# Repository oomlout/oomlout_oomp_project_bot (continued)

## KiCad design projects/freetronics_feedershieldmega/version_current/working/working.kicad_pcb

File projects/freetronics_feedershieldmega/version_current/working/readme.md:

# OOMP Project  
## FeederShieldMega  by freetronics  
  
oomp key: oomp_projects_flat_freetronics_feedershieldmega  
(snippet of original readme)  
  
Feeder Shield Mega  
==================  
Copyright 2018-2020 Freetronics Pty Ltd  www.freetronics.com    
  
Pick and place feeder controller for DIY feeders. Compatible with the  
0816 feeders designed by MGRL:  
  
  https://docs.mgrl.de/maschine:pickandplace:feeder:0816feeder  
  
These feeders are commonly used with DIY pick and place machines  
running OpenPNP:  
  
  http://openpnp.org  
  
Run the MGRL feeder control firmware.  
  
Adds an I2C display that can be used for reporting events and part  
counts.  
  
Uses 10-way IDC cables to connect batches of 4 feeders. Mates to the  
MGRL0816 Feeder Link board, which bridges across the 4-pin connections  
on 4 feeders mounted side by side.  
  
Features:  
  
 * 24 feeder outputs  
 * PWM output and feedback input  
 * GND and 5V supply to feeders  
 * Software controlled feeder power  
 * 128x32 OLED  
  
You can view more online at:  
  
  http://www.freetronics.com.au/fsm  

INSTALLATION  
------------  
The design is saved as an EAGLE project. EAGLE PCB design software is  
available from www.cadsoftusa.com free for non-commercial use. To use  
this project download it and place the directory containing these files  
into the "eagle" directory on your computer. Then open EAGLE and  
navigate to the project.  

DISTRIBUTION  
------------  
The specific terms of distribution of this project are governed by the  
license referenced below.  

LICENSE  
-------  
Licensed under the TAPR Open Hardware License (www.tapr.org/OHL).  
The "license" folder within this repository also contains a copy of  
this license i  
  full source readme at [readme_src.md](readme_src.md)  
  
source repo at: [https://github.com/freetronics/FeederShieldMega](https://github.com/freetronics/FeederShieldMega)  
## Board  

## Schematic  

[schematic pdf](working_schematic.pdf)  
## Images

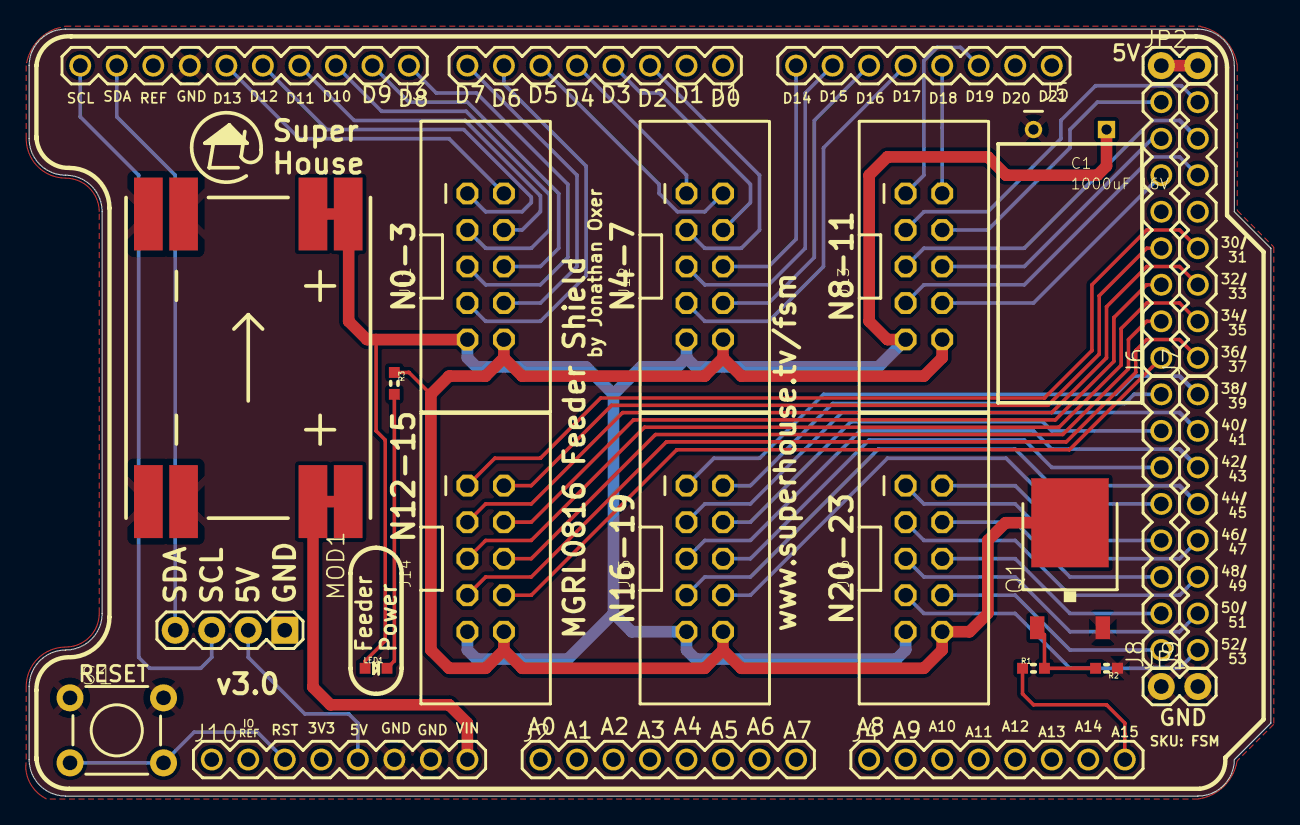
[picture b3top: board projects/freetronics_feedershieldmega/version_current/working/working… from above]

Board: 2 copper layers, 86.4 x 53.3 mm, 27 parts (0 on the bottom side), 60 nets.

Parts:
C1: 1000uF 16V; CPOL-RADIAL-5.08-10X18-FLAT
J1, J5: Digital_0_7; 1X08-P-BELOW
J2, J4: Analog; 1X08-P-BELOW
J3: Digital_8_13; 1X10-P-BELOW
J6: Digital_22_36; 1X08-P-BELOW
J7: Digital_23_37; 1X08-P-BELOW
J8: Digital_38_52; 1X08-P-BELOW
J9: Digital_39_53; 1X08-P-BELOW
J10: Power; 1X08-P-BELOW
J11, J12, J13, J14, J15, J16: M02X5-SHROUDED; 2X05-2.54-SHROUDED
JP1, JP2: 1X02-P-BELOW
LED1: GREEN; LED-0603
MOD1: OLED-I2C128X32-0.91-HEADER; OLED-128X32-0.91-HEADER
MOD2: DC5V3A-SMT
Q1: NTD5867NLT4G; DPACK
R1: 1K; R0603
R2: 10K; R0603
R3: 470R; R0603
S1: TACTILE-PTH-6MM

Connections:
5V: J10.5, MOD1.VCC
5V_2: JP2.1, JP2.2
A15: J4.8, R1.1
D2: J1.3, J12.3
D3: J1.4, J12.4
D4: J1.5, J12.1
D5: J1.6, J12.2
D6: J1.7, J11.7
D7: J1.8, J11.8
D8: J3.1, J11.5
D9: J3.2, J11.6
D10: J3.3, J11.3
D11_MOSI: J3.4, J11.4
D12_MISO: J3.5, J11.1
D13_SCK: J3.6, J11.2
D14: J5.8, J12.6
D15: J5.7, J12.5
D16: J5.6, J12.8
D17: J5.5, J12.7
D18: J5.4, J13.2
D19: J5.3, J13.1
D22: J6.8, J13.4
D23: J7.8, J13.3
D24: J6.7, J13.6
D25: J7.7, J13.5
D26: J6.6, J13.8
D27: J7.6, J13.7
D30: J6.4, J14.2
D31: J7.4, J14.1
D32: J6.3, J14.4
D33: J7.3, J14.3
D34: J6.2, J14.6
D35: J7.2, J14.5
D36: J6.1, J14.8
D37: J7.1, J14.7
D38: J8.8, J15.2
D39: J9.8, J15.1
D40: J8.7, J15.4
D41: J9.7, J15.3
D42: J8.6, J15.6
D43: J9.6, J15.5
D44: J8.5, J15.8
D45: J9.5, J15.7
D46: J8.4, J16.2
D47: J9.4, J16.1
D48: J8.3, J16.4
D49: J9.3, J16.3
D50_MISO: J8.2, J16.6
D51_MOSI: J9.2, J16.5
D52_SCK: J8.1, J16.8
D53: J9.1, J16.7
F_5V: C1.1, J11.9, J12.9, J13.9, J14.9, J15.9, J16.9, LED1.A, MOD2.3A, MOD2.3B
F_GND: J11.10, J12.10, J13.10, J14.10, J15.10, J16.10, Q1.2, R3.1
GND: C1.2, J3.7, J10.6, J10.7, JP1.1, JP1.2, MOD1.GND, MOD2.1A, MOD2.1B, MOD2.4A, MOD2.4B, Q1.3, R2.1, S1.1, S1.2
unnamed: Q1.1, R1.2, R2.2
unnamed: LED1.C, R3.2
RESET: J10.3, S1.3, S1.4
SCL: J3.10, MOD1.SCL
SDA: J3.9, MOD1.SDA
VIN: J10.8, MOD2.2A, MOD2.2B

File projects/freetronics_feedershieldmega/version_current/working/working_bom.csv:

"Id";"Designator";"Footprint";"Quantity";"Designation";"Supplier and ref";
1;"JP2,JP1";"1X02-P-BELOW";2;"";;;
2;"J12,J13,J11,J14,J15,J16";"2X05-2.54-SHROUDED";6;"M02X5-SHROUDED";;;
3;"J9";"1X08-P-BELOW";1;"Digital_39_53";;;
4;"J10";"1X08-P-BELOW";1;"Power";;;
5;"R3";"R0603";1;"470R";;;
6;"R2";"R0603";1;"10K";;;
7;"J3";"1X10-P-BELOW";1;"Digital_8_13";;;
8;"C1";"CPOL-RADIAL-5.08-10X18-FLAT";1;"1000uF 16V";;;
9;"J2,J4";"1X08-P-BELOW";2;"Analog";;;
10;"LED1";"LED-0603";1;"GREEN";;;
11;"R1";"R0603";1;"1K";;;
12;"J5,J1";"1X08-P-BELOW";2;"Digital_0_7";;;
13;"MOD2";"DC5V3A-SMT";1;"DC5V3A-SMT";;;
14;"J7";"1X08-P-BELOW";1;"Digital_23_37";;;
15;"J8";"1X08-P-BELOW";1;"Digital_38_52";;;
16;"J6";"1X08-P-BELOW";1;"Digital_22_36";;;
17;"Q1";"DPACK";1;"NTD5867NLT4G";;;
18;"MOD1";"OLED-128X32-0.91-HEADER";1;"OLED-I2C128X32-0.91-HEADER";;;
19;"S1";"TACTILE-PTH-6MM";1;"";;;

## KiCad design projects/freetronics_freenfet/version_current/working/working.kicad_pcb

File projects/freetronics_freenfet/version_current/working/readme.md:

# FREENFET by freetronics  
This is a harvested standardized copy of a project from github.  
The original project can be found at:  
https://github.com/freetronics/FREENFET  
Please consult that link for additional, details, files, and license information.  
Note: It was auto harvested and if the original repo had more than one board file or anything out of the ordinary the files here are likely not representative.

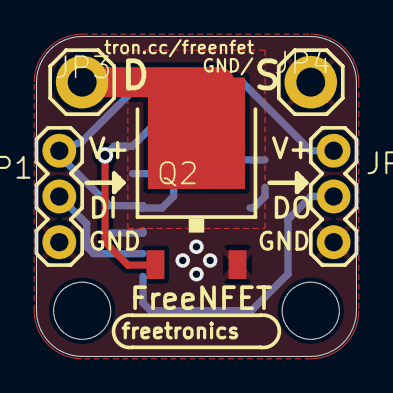
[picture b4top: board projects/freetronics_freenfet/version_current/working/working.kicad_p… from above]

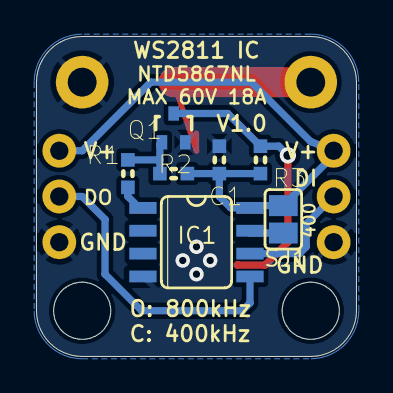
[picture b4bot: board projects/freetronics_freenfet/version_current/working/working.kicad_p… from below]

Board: 2 copper layers, 17.8 x 17.8 mm, 14 parts (7 on the bottom side), 9 nets.

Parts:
@HOLE0, @HOLE1: (no value)
C1: 1uF 0603; 0603
IC1: WS2811-SOP8; SO08-SKINNYPADS
JP1: IN; 1X03
JP2: OUT; 1X03
JP3: DRAIN; 1X01LARGE
JP4: SOURCE; 1X01LARGE
Q1: RJU003N03; SOT32-3
Q2: NTD5867NLT4G; DPACK
R1: 1K; 0603
R2, R3: 10K; 0603
SJ1: LOW-SPEED; SJ

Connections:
D: JP3.1, Q2.2
DIN: IC1.6, JP1.2
DOUT: IC1.5, JP2.2
GND: C1.2, IC1.4, JP1.3, JP2.3, JP4.1, Q1.2, Q2.3
unnamed: IC1.7, SJ1.1
unnamed: Q1.1, R1.1, R2.1
unnamed: Q1.3, Q2.1, R3.1
OUT1: IC1.1, R1.2
VCC: C1.1, IC1.8, JP1.1, JP2.1, R2.2, R3.2, SJ1.2

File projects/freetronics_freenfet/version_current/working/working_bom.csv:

"Id";"Designator";"Footprint";"Quantity";"Designation";"Supplier and ref";
1;"JP1";"1X03";1;"IN";;;
2;"JP4";"1X01LARGE";1;"SOURCE";;;
3;"JP2";"1X03";1;"OUT";;;
4;"JP3";"1X01LARGE";1;"DRAIN";;;
5;"Q2";"DPACK";1;"NTD5867NLT4G";;;
6;"@HOLE1,@HOLE0";"";2;"";;;
7;"Q1";"SOT32-3";1;"RJU003N03";;;
8;"IC1";"SO08-SKINNYPADS";1;"WS2811-SOP8";;;
9;"R1";"0603";1;"1K";;;
10;"SJ1";"SJ";1;"LOW-SPEED";;;
11;"C1";"0603";1;"1uF 0603";;;
12;"R3,R2";"0603";2;"10K";;;

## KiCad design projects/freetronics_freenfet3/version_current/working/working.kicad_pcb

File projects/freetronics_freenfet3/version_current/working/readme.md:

# FREENFET3 by freetronics  
This is a harvested standardized copy of a project from github.  
The original project can be found at:  
https://github.com/freetronics/FREENFET3  
Please consult that link for additional, details, files, and license information.  
Note: It was auto harvested and if the original repo had more than one board file or anything out of the ordinary the files here are likely not representative.

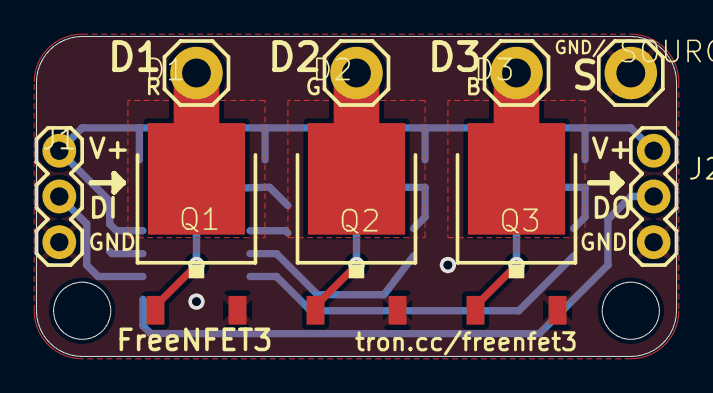
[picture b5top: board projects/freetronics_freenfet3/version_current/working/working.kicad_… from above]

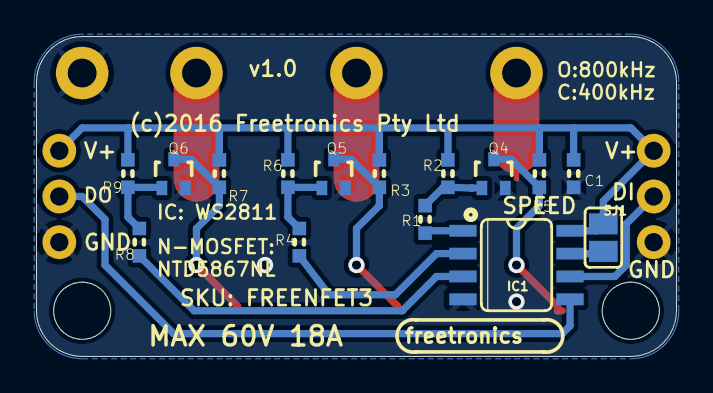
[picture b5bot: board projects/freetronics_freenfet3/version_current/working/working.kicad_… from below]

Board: 2 copper layers, 35.6 x 17.8 mm, 26 parts (15 on the bottom side), 17 nets.

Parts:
@HOLE0, @HOLE1: (no value)
C1: 1uF; 0603
D1, D2, D3: DRAIN; 1X01LARGE
IC1: WS2811-SOP8; SO08-SKINNYPADS
J1: IN; 1X03
J2: OUT; 1X03
Q1, Q2, Q3: NTD5867NLT4G; DPACK
Q4, Q5, Q6: RJU003N03; SOT32-3
R1, R4, R8: 1K; 0603
R2, R3, R5, R6, R7, R9: 10K; 0603
SJ1: LOW-SPEED; SJ
SOURCE0: SOURCE; 1X01LARGE

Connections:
D: D1.1, Q1.2
D1: D2.1, Q2.2
D2: D3.1, Q3.2
DIN: IC1.6, J1.2
DOUT: IC1.5, J2.2
GND: C1.2, IC1.4, J1.3, J2.3, Q1.3, Q2.3, Q3.3, Q4.2, Q5.2, Q6.2, SOURCE0.1
unnamed: Q2.1, Q5.3, R3.1
unnamed: Q4.1, R1.1, R2.1
unnamed: Q1.1, Q4.3, R5.1
unnamed: Q5.1, R4.1, R6.1
unnamed: Q3.1, Q6.3, R7.1
unnamed: Q6.1, R8.1, R9.1
unnamed: IC1.7, SJ1.1
OUT1: IC1.1, R1.2
OUT2: IC1.2, R4.2
OUT3: IC1.3, R8.2
VCC: C1.1, IC1.8, J1.1, J2.1, R2.2, R3.2, R5.2, R6.2, R7.2, R9.2, SJ1.2

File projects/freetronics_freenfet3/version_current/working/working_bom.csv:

"Id";"Designator";"Footprint";"Quantity";"Designation";"Supplier and ref";
1;"SOURCE0";"1X01LARGE";1;"SOURCE";;;
2;"D2,D3,D1";"1X01LARGE";3;"DRAIN";;;
3;"J1";"1X03";1;"IN";;;
4;"@HOLE0,@HOLE1";"";2;"";;;
5;"Q3,Q2,Q1";"DPACK";3;"NTD5867NLT4G";;;
6;"J2";"1X03";1;"OUT";;;
7;"R6,R5,R2,R9,R7,R3";"0603";6;"10K";;;
8;"IC1";"SO08-SKINNYPADS";1;"WS2811-SOP8";;;
9;"R1,R4,R8";"0603";3;"1K";;;
10;"SJ1";"SJ";1;"LOW-SPEED";;;
11;"Q6,Q5,Q4";"SOT32-3";3;"RJU003N03";;;
12;"C1";"0603";1;"1uF";;;

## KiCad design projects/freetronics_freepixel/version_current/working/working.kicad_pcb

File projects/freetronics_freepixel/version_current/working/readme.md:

# FREEPIXEL by freetronics  
This is a harvested standardized copy of a project from github.  
The original project can be found at:  
https://github.com/freetronics/FREEPIXEL  
Please consult that link for additional, details, files, and license information.  
Note: It was auto harvested and if the original repo had more than one board file or anything out of the ordinary the files here are likely not representative.

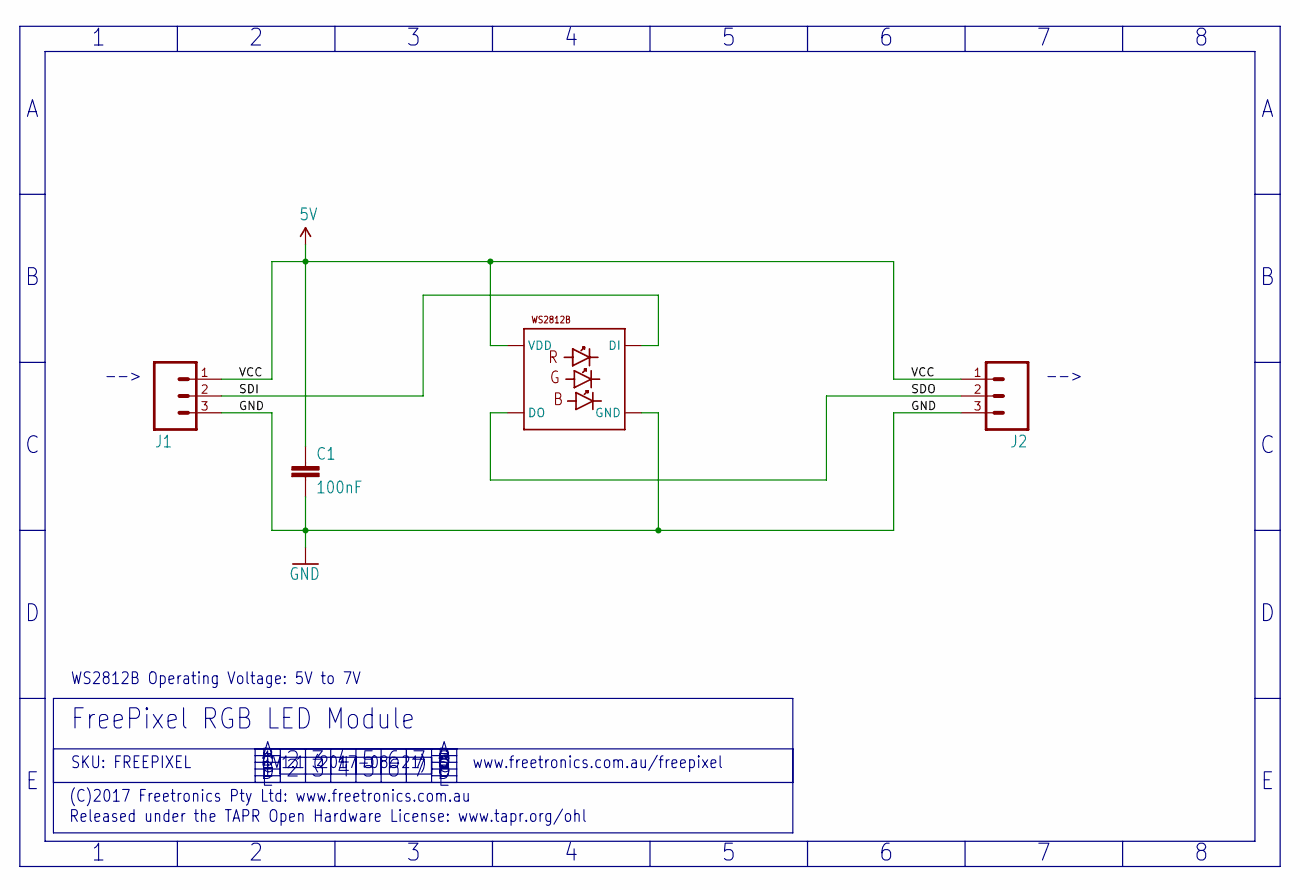
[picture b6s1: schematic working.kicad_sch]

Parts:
C1: 100nF; 0603
J1, J2: M03PTH; 1X03
LED1: WS2812B5050; WS2812B

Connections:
GND: C1.2, J1.3, J2.3, LED1.3-GND (GND)
SDI: J1.2, LED1.4-DIN (DI)
SDO: J2.2, LED1.2-DOUT (DO)
VCC: C1.1, J1.1, J2.1, LED1.1-VDD (VDD)

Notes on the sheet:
www.freetronics.com.au/freepixel
WS2812B Operating Voltage: 5V to 7V
Released under the TAPR Open Hardware License: www.tapr.org/ohl
FreePixel RGB LED Module
(C)2017 Freetronics Pty Ltd: www.freetronics.com.au
-->
SKU: FREEPIXEL
V1.1 (2017-08-21)

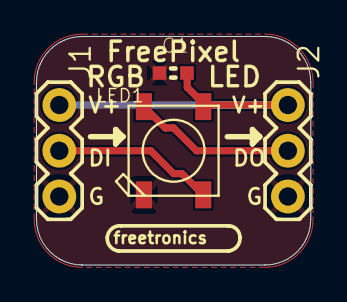
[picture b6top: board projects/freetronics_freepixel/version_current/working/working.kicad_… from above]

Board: 2 copper layers, 15.2 x 12.7 mm, 4 parts (0 on the bottom side), 4 nets.

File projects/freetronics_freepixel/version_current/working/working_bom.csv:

"Id";"Designator";"Footprint";"Quantity";"Designation";"Supplier and ref";
1;"J2,J1";"1X03";2;"";;;
2;"LED1";"WS2812B";1;"WS2812B5050";;;
3;"C1";"0603";1;"100nF";;;

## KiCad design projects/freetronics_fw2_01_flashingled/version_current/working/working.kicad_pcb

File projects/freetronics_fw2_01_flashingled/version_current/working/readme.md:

# OOMP Project  
## FW2-01-FlashingLED  by freetronics  
  
oomp key: oomp_projects_flat_freetronics_fw2_01_flashingled  
(snippet of original readme)  
  
Flashing LED  
============  
Copyright 2016 Freetronics Pty Ltd    
Freetronics site:  http://www.freetronics.com.au    
Freetronics email: <info@freetronics.com>    
  
Based on the project "Multi Purpose Flashing LED" described in the book  
"Funway Into Electronics Volume 2" by Dick Smith.  
  
Flashes an LED. Optionally flashes 2 LEDs alternating.  
  
More information is available at:  
  
  http://www.freetronics.com.au/fw2-flash    

INSTALLATION  
------------  
The design is saved as an EAGLE project. EAGLE PCB design software is  
available from www.cadsoftusa.com free for non-commercial use. To use  
this project download it and place the directory containing these files  
into the "eagle" directory on your computer.  

DISTRIBUTION  
------------  
The specific terms of distribution of this project are governed by the  
license referenced below.  

LICENSE  
-------  
Licensed under the TAPR Open Hardware License (www.tapr.org/OHL).  
The "license" folder within this repository also contains a copy of  
this license in plain text format.  
  
  full source readme at [readme_src.md](readme_src.md)  
  
source repo at: [https://github.com/freetronics/FW2-01-FlashingLED](https://github.com/freetronics/FW2-01-FlashingLED)  
## Board  

## Schematic  

[schematic pdf](working_schematic.pdf)  
## Images

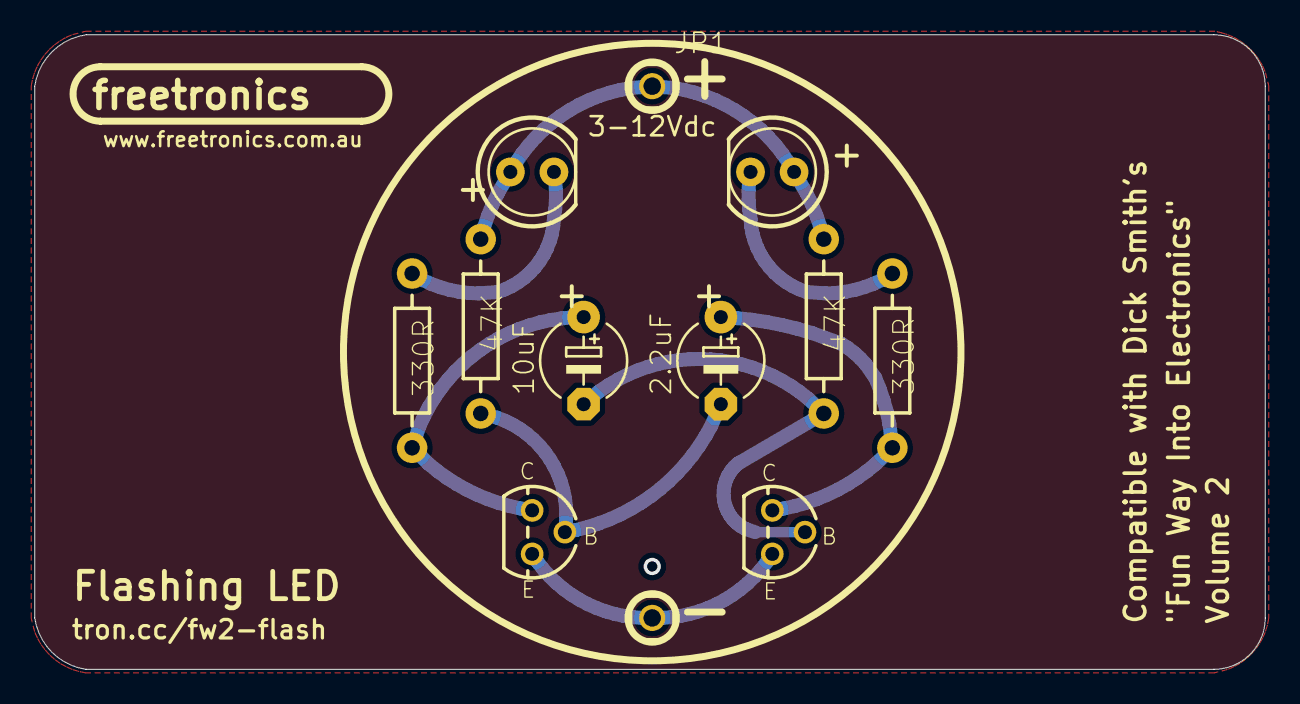
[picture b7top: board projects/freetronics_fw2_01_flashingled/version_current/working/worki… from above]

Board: 6 copper layers, 71.7 x 37.0 mm, 12 parts (0 on the bottom side), 8 nets.

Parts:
C1: 10uF; E5-5
C2: 2.2uF; E5-5
JP1: PWR+; 1X01
JP2: PWR-; 1X01
LED1, LED2: LED5MMLARGE
Q1, Q2: BC548; TO-92
R1, R4: 330R; AXIAL-0.4-LARGE
R2, R3: 47K; AXIAL-0.4-LARGE

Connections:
GND: LED1.K, R1.P$2
unnamed: JP1.1, LED1.A, LED2.A, R2.P$2, R3.P$2
unnamed: C1.+, Q1.1, R1.P$1
unnamed: C2.+, Q2.1, R4.P$1
unnamed: C2.-, Q1.2, R3.P$1
unnamed: C1.-, Q2.2, R2.P$1
unnamed: JP2.1, Q1.3, Q2.3
unnamed: LED2.K, R4.P$2

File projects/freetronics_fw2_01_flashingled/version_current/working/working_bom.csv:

"Id";"Designator";"Footprint";"Quantity";"Designation";"Supplier and ref";
1;"C1";"E5-5";1;"10uF";;;
2;"Q1,Q2";"TO-92";2;"BC548";;;
3;"R3,R2";"AXIAL-0.4-LARGE";2;"47K";;;
4;"R4,R1";"AXIAL-0.4-LARGE";2;"330R";;;
5;"LED1,LED2";"LED5MMLARGE";2;"";;;
6;"JP1";"1X01";1;"PWR+";;;
7;"C2";"E5-5";1;"2.2uF";;;
8;"JP2";"1X01";1;"PWR-";;;

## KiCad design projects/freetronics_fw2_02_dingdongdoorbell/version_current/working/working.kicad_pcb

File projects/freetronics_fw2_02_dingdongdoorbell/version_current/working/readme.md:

# FW2-02-DingDongDoorbell by freetronics  
This is a harvested standardized copy of a project from github.  
The original project can be found at:  
https://github.com/freetronics/FW2-02-DingDongDoorbell  
Please consult that link for additional, details, files, and license information.  
Note: It was auto harvested and if the original repo had more than one board file or anything out of the ordinary the files here are likely not representative.

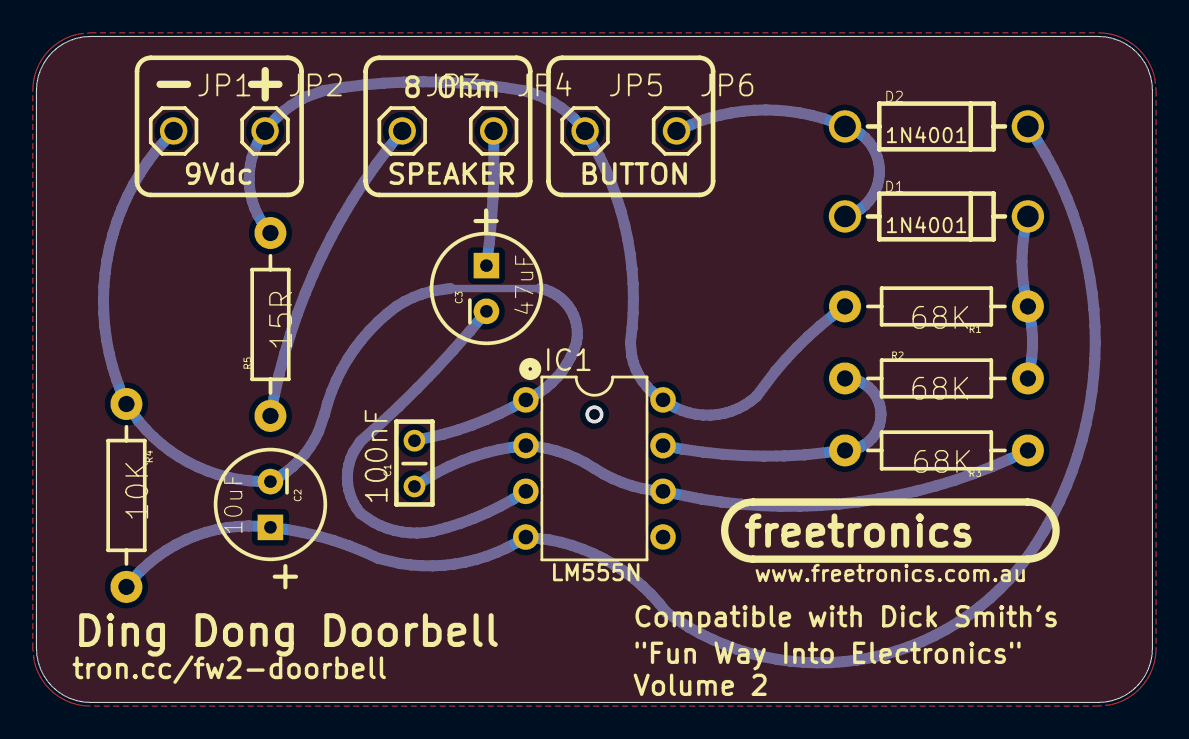
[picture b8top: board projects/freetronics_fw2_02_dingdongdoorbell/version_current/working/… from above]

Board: 6 copper layers, 62.0 x 37.0 mm, 17 parts (0 on the bottom side), 10 nets.

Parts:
C1: 100nF; CAP-PTH-SMALL
C2: 10uF; CPOL-RADIAL-10UF-25V
C3: 47uF; CPOL-RADIAL-10UF-25V
D1, D2: 1N4001; DIODE-1N4001
IC1: 555L; DIL08L
JP1, JP5, JP6: PWR-; 1X01
JP2: PWR+; 1X01
JP3: SPKR+; 1X01
JP4: SPKR-; 1X01
R1, R2, R3: 68K; AXIAL-0.4-LARGE
R4: 10K; AXIAL-0.4-LARGE
R5: 15R; AXIAL-0.4-LARGE

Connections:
GND: D1.C, R1.P$1, R2.P$2
unnamed: IC1.7, R2.P$1, R3.P$2
unnamed: D1.A, D2.A, JP6.1
unnamed: IC1.8, JP2.1, JP5.1, R1.P$2, R5.P$2
unnamed: JP3.1, R5.P$1
unnamed: C3.1, JP4.1
unnamed: C3.2, IC1.3
unnamed: C2.1, D2.C, IC1.4, R4.P$2
unnamed: C1.2, C2.2, IC1.1, JP1.1, R4.P$1
unnamed: C1.1, IC1.2, IC1.6, R3.P$1

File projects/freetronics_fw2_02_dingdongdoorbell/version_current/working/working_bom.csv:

"Id";"Designator";"Footprint";"Quantity";"Designation";"Supplier and ref";
1;"JP5,JP1,JP6";"1X01";3;"PWR-";;;
2;"C2";"CPOL-RADIAL-10UF-25V";1;"10uF";;;
3;"D2,D1";"DIODE-1N4001";2;"1N4001";;;
4;"C1";"CAP-PTH-SMALL";1;"100nF";;;
5;"IC1";"DIL08L";1;"555L";;;
6;"JP3";"1X01";1;"SPKR+";;;
7;"JP2";"1X01";1;"PWR+";;;
8;"R3,R1,R2";"AXIAL-0.4-LARGE";3;"68K";;;
9;"C3";"CPOL-RADIAL-10UF-25V";1;"47uF";;;
10;"JP4";"1X01";1;"SPKR-";;;
11;"R5";"AXIAL-0.4-LARGE";1;"15R";;;
12;"R4";"AXIAL-0.4-LARGE";1;"10K";;;
